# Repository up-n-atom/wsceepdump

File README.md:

# Just Enough WonderSwan Color/Swan Crystal EEPROM dumper

_⚠️ USE WITH CAUTION! Always test on a handheld of lesser importance to confirm its operation_

On each boot the bootrom writes to the EEPROM, removing the authenticity of the factory default. Such writes include the _"unique"_ cartridge count, boot count, and previously booted cartridge identifier. If these are not important, a custom rom and serial cable is the more convenient alternative, eg. https://github.com/asiekierka/ws-ieepview

> Fun Fact: The SwanCrystal EEPROM contains the Bandai bootsplash present in the bootrom.

## Components

> Shop around, AliExpress links are non-affiliated top searches.

* 1x Blue Pill [[AliExpress](https://www.aliexpress.com/item/32792513237.html)]
* 1x ST-Link<sup>1</sup> or USB to TTL<sup>2</sup> [[AliExpress<sup>1</sup>](https://www.aliexpress.com/item/32887597480.html) or [AliExpress<sup>2</sup>](https://www.aliexpress.com/item/32946781917.html)]
* 1x SOP8 Test Clip [[AliExpress](https://www.aliexpress.com/item/32968334401.html)]
* 1x Breadboard [[AliExpress](https://www.aliexpress.com/item/32430469610.html)]
* 7x Male to Male Dupont Cables [[AliExpress](https://www.aliexpress.com/item/4000203371860.html)]
* 1x 1.2K Resistor [[AliExpress](https://www.aliexpress.com/item/32847096736.html)]

## Arduino Bootloader

There are nemerous guides on how to install the STM32duino bootloader and the following [video](https://www.youtube.com/watch?v=Myon8H111PQ) does an excellent job of describing the process.

Additionally, you may require the [STM32 Virtual COM Port Driver](https://www.st.com/en/development-tools/stsw-stm32102.html).

## Wiring

| Blue Pill | Test Clip | EEPROM     |
|-----------|-----------|------------|
| A4        | 1         | CS         |
| A5        | 2         | SK         |
| A6        | 3         | DI         |
| A7        | 4         | DO         |
| G         | 5         | GND        |
| 3.3       | 8         | VCC        |

1.2K pull-down resistor connected to pin 1 (Chip Select) and pin 5 (Ground) of the test clip.

_Optional: 1.5K pull-up resistor connected to pin 4 (DO) and pin 8 (VCC) of the test clip._

## Cape

## Usage

1. Upload the [Arduino sketch](/arduino/wsc.ino) and run the Arduino IDE Serial Monitor or any alternative serial terminal such as [Tera Term](https://ttssh2.osdn.jp/index.html.en) or [Putty](https://www.putty.org/).
2. Send an **r** character to read the EEPROM.
3. Select all and copy the hex output.
4. Paste the copied hex output as _hex_ into a Hex Editor such as https://hexed.it/ or [HxD](https://mh-nexus.de/en/hxd/)
5. Save As...

## Testing

[Higan](https://higan.dev/) is able to load and emulate your EEPROM dump by renaming it as _save.eeprom_ and moving it into the _Systems/WonderSwan Color_ or _Systems/SwanCrystal_ directories.

## Custom Bootsplash

### WonderSwan Color

https://github.com/up-n-atom/higan/tree/ws-bootsplash/higan/System/WonderSwan%20Color

* [x] Dengeki
* [x] NAVI GET 400 Million
* [x] MS-06S Zaku II
* [x] RX-78-2
* [ ] Inuyasha
* [ ] Growlmon

### SwanCrystal

https://github.com/up-n-atom/higan/tree/ws-bootsplash/higan/System/SwanCrystal

* [x] One Piece Grand Battle Swan Colosseum 
* [ ] Tanita Mama Mitte

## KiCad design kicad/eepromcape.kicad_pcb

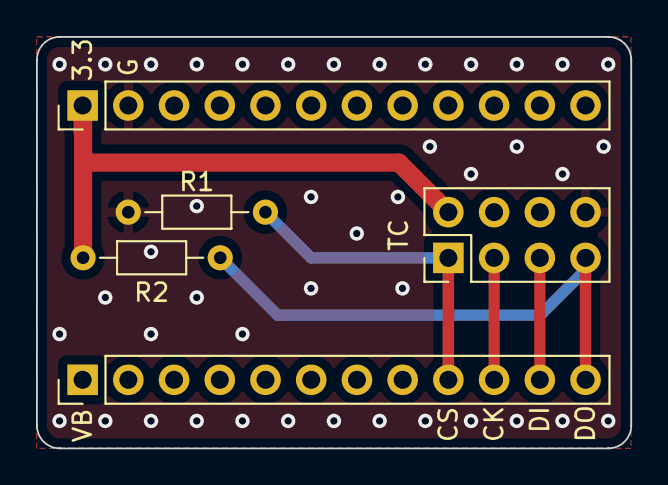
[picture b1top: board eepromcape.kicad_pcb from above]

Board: 2 copper layers, 33.0 x 22.9 mm, 5 parts (1 on the bottom side), 6 nets.

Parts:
3.3: Conn_01x12; PinHeader_1x12_P2.54mm_Vertical
R1: 1K2; R_Axial_DIN0204_L3.6mm_D1.6mm_P7.62mm_Horizontal
R2: 1K5; R_Axial_DIN0204_L3.6mm_D1.6mm_P7.62mm_Horizontal
TC: Conn_02x04_Counter_Clockwise; PinSocket_2x04_P2.54mm_Vertical
VB: Conn_01x12; PinHeader_1x12_P2.54mm_Vertical

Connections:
+3V3: 3.3.1, R2.2, TC.8
CK: TC.2, VB.10
CS: R1.1, TC.1, VB.9
DI: TC.3, VB.11
DO: R2.1, TC.4, VB.12
GND: 3.3.2, R1.2, TC.5

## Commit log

2021-03-21 Add Arduino sketch
2021-03-21 Add images
2021-03-24 Add SwanCrystal EEPROM image
2021-03-25 Add KiCAD project
2021-03-25 Remove superfluous power traces
2021-03-26 Fix 3D models
2021-03-26 Add write routines
2022-04-26 Use DELAY_MS for writing
2023-01-27 Add cape image
2023-01-27 Add WonderSwan support
2023-01-27 Fix size declaration
2023-01-27 Fix size parenthesis
2023-01-28 Simplify size
